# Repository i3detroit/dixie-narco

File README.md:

# dixie-narco
Replacement controller for a Dixie-Narco drink vending machine

Initial reverse-engineering and machine details located in the history of the [equipment page](https://www.i3detroit.org/wiki/Dixie_Narco_Soda_Machine), which will be a living document for the current status of the machine.

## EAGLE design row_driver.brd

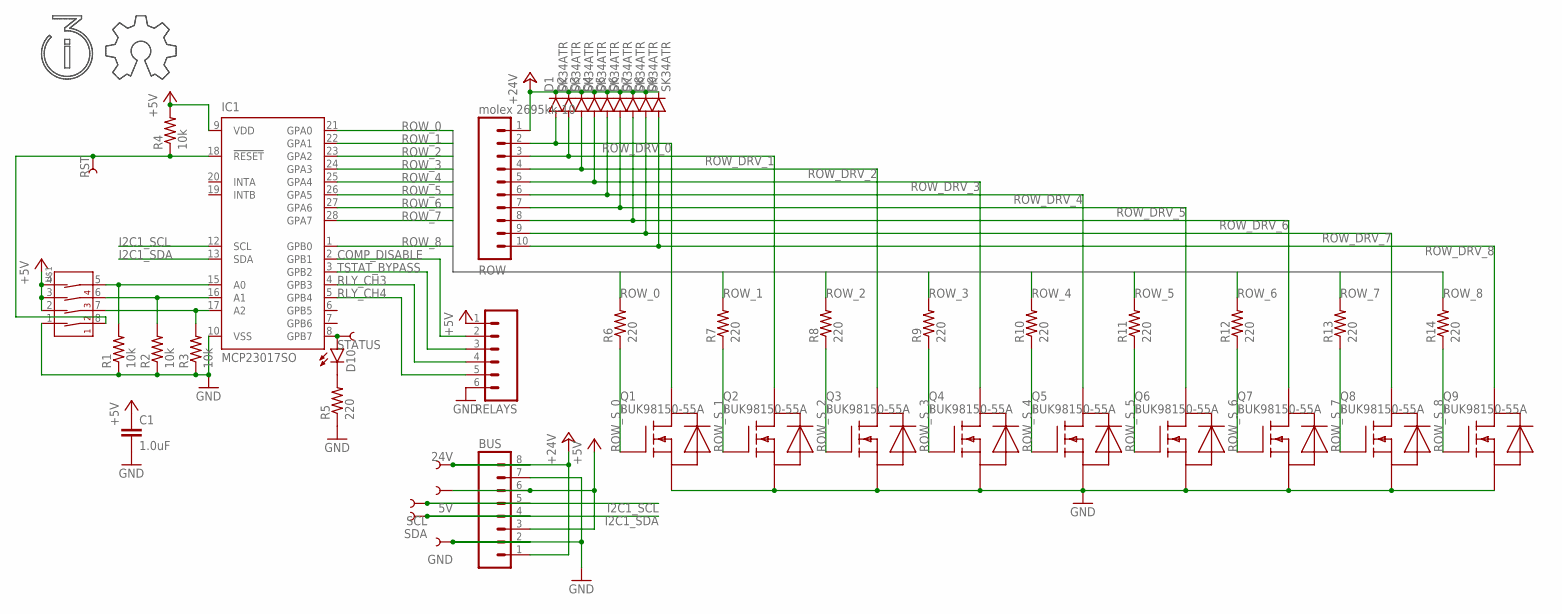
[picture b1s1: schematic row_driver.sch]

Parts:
5V, 24V: TEST-POINTTP_15TH_THRU; TP_15TH
BUS: M08FEMALE_LOCK; 1X08_FEMALE_LOCK
C1: 1.0uF; 0603-CAP
D1, D2, D3, D4, D5, D6, D7, D8, D9: SK34ATR; SMA-DIODE
D10: LED1206; LED-1206
GND: TEST-POINTTP_15TH_THRU; TP_15TH
IC1: MCP23017SO; SO28W
Q1, Q2, Q3, Q4, Q5, Q6, Q7, Q8, Q9: BUK98150-55A; SOT223
R1, R2, R3, R4: 10k; 0805
R5, R6, R7, R8, R9, R10, R11, R12, R13, R14: 220; 0805
RELAYS: M06LOCK; 1X06_LOCK
ROW: molex 2695kk-10; 1X10_LOCK
RST: TEST-POINTTP_15TH_THRU; TP_15TH
SCL: TEST-POINTTP_15TH_THRU; TP_15TH
SDA: TEST-POINTTP_15TH_THRU; TP_15TH
STATUS: TEST-POINTTP_15TH_THRU; TP_15TH
U$1: 4-POS-DIP; 4-POS-DIP-SMD
U$2: I3LOGO
U$4: OSHWLOGO

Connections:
+5V: 5V.P$1, BUS.3, BUS.6, C1.1, IC1.9 (VDD), R4.2, RELAYS.1, U$1.2 (2A), U$1.3 (3A), U$1.4 (4A)
+24V: 24V.P$1, BUS.1, BUS.8, D1.C, D2.C, D3.C, D4.C, D5.C, D6.C, D7.C, D8.C, D9.C, ROW.1
A0: IC1.15 (A0), R1.2, U$1.5 (4B)
A1: IC1.16 (A1), R2.2, U$1.6 (3B)
A2: IC1.17 (A2), R3.2, U$1.7 (2B)
COMP_DISABLE: IC1.2 (GPB1), RELAYS.2
GND: BUS.2, BUS.7, C1.2, GND.P$1, IC1.10 (VSS), Q1.3 (S), Q2.3 (S), Q3.3 (S), Q4.3 (S), Q5.3 (S), Q6.3 (S), Q7.3 (S), Q8.3 (S), Q9.3 (S), R1.1, R2.1, R3.1, R5.1, RELAYS.6, U$1.1 (1A)
I2C1_SCL: BUS.5, IC1.12 (SCL), SCL.P$1
I2C1_SDA: BUS.4, IC1.13 (SDA), SDA.P$1
unnamed: D10.C, R5.2
RLY_CH3: IC1.4 (GPB3), RELAYS.4
RLY_CH4: IC1.5 (GPB4), RELAYS.5
ROW_0: IC1.21 (GPA0), R6.2
ROW_1: IC1.22 (GPA1), R7.2
ROW_2: IC1.23 (GPA2), R8.2
ROW_3: IC1.24 (GPA3), R9.2
ROW_4: IC1.25 (GPA4), R10.2
ROW_5: IC1.26 (GPA5), R11.2
ROW_6: IC1.27 (GPA6), R12.2
ROW_7: IC1.28 (GPA7), R13.2
ROW_8: IC1.1 (GPB0), R14.2
ROW_DRV_0: D1.A, Q1.2 (D), Q1.4 (D), ROW.2
ROW_DRV_1: D2.A, Q2.2 (D), Q2.4 (D), ROW.3
ROW_DRV_2: D3.A, Q3.2 (D), Q3.4 (D), ROW.4
ROW_DRV_3: D4.A, Q4.2 (D), Q4.4 (D), ROW.5
ROW_DRV_4: D5.A, Q5.2 (D), Q5.4 (D), ROW.6
ROW_DRV_5: D6.A, Q6.2 (D), Q6.4 (D), ROW.7
ROW_DRV_6: D7.A, Q7.2 (D), Q7.4 (D), ROW.8
ROW_DRV_7: D8.A, Q8.2 (D), Q8.4 (D), ROW.9
ROW_DRV_8: D9.A, Q9.2 (D), Q9.4 (D), ROW.10
ROW_S_0: Q1.1 (G), R6.1
ROW_S_1: Q2.1 (G), R7.1
ROW_S_2: Q3.1 (G), R8.1
ROW_S_3: Q4.1 (G), R9.1
ROW_S_4: Q5.1 (G), R10.1
ROW_S_5: Q6.1 (G), R11.1
ROW_S_6: Q7.1 (G), R12.1
ROW_S_7: Q8.1 (G), R13.1
ROW_S_8: Q9.1 (G), R14.1
RST: IC1.18 (!RESET), R4.1, RST.P$1, U$1.8 (1B)
STATUS: D10.A, IC1.8 (GPB7), STATUS.P$1
TSTAT_BYPASS: IC1.3 (GPB2), RELAYS.3

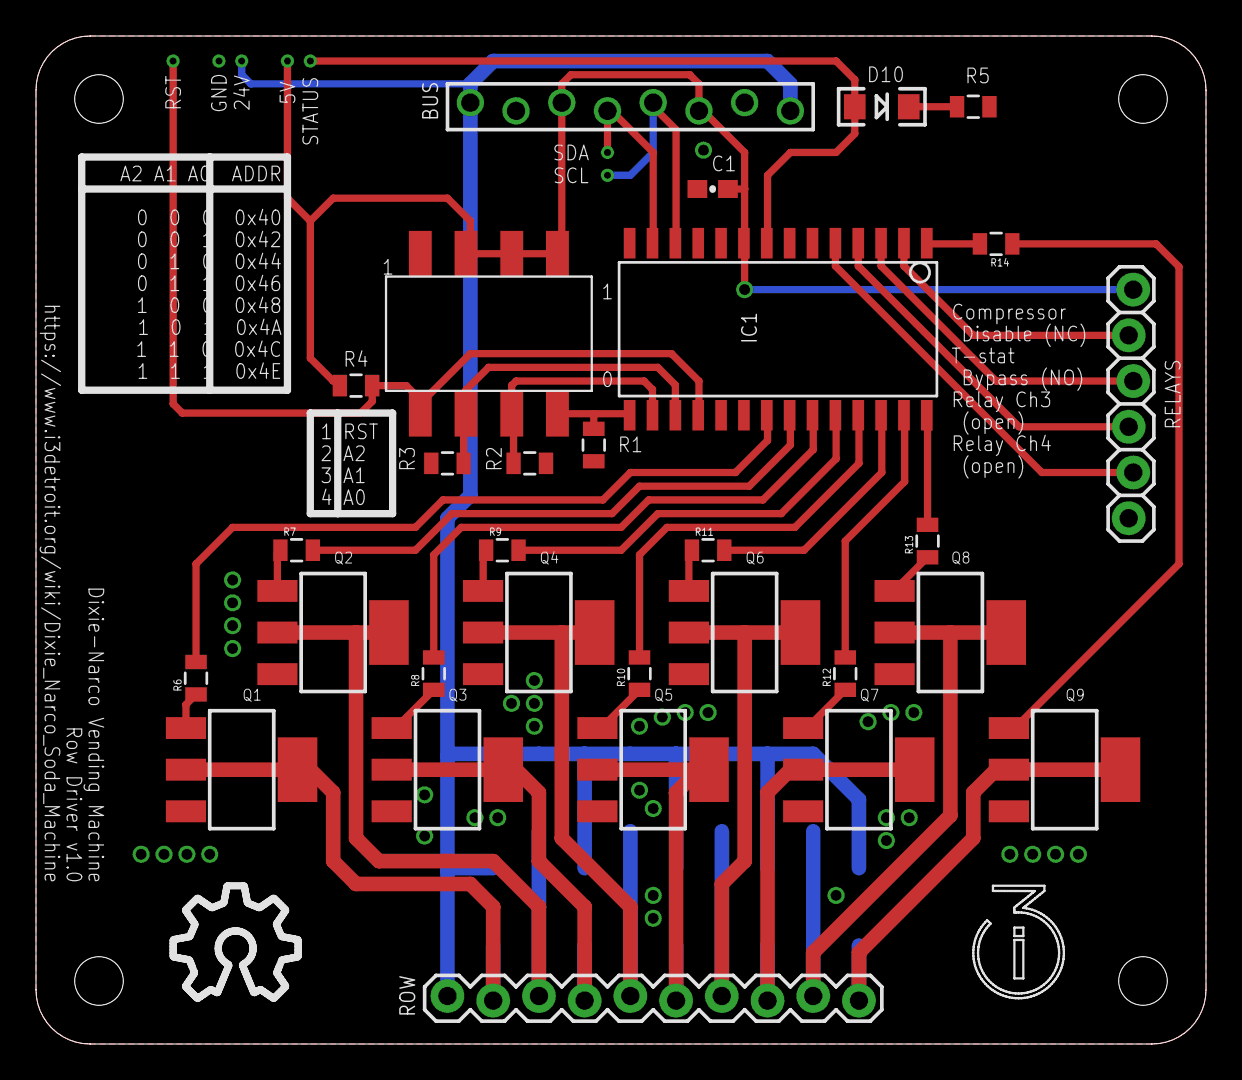
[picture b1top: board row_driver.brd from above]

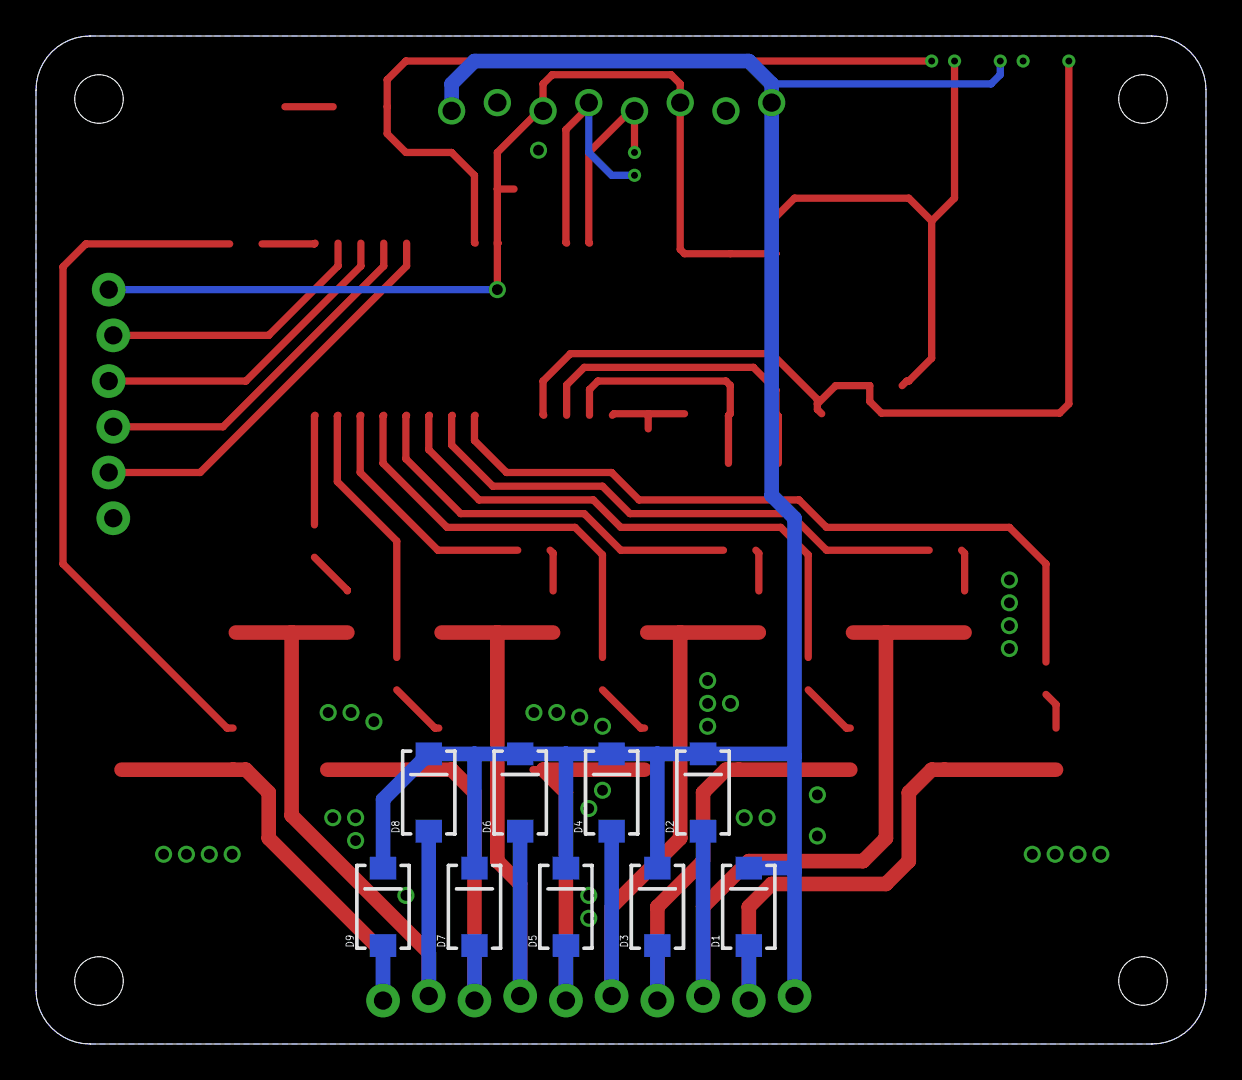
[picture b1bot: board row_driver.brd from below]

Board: 2 copper layers, 65.0 x 56.0 mm, 48 parts (9 on the bottom side), 42 nets.

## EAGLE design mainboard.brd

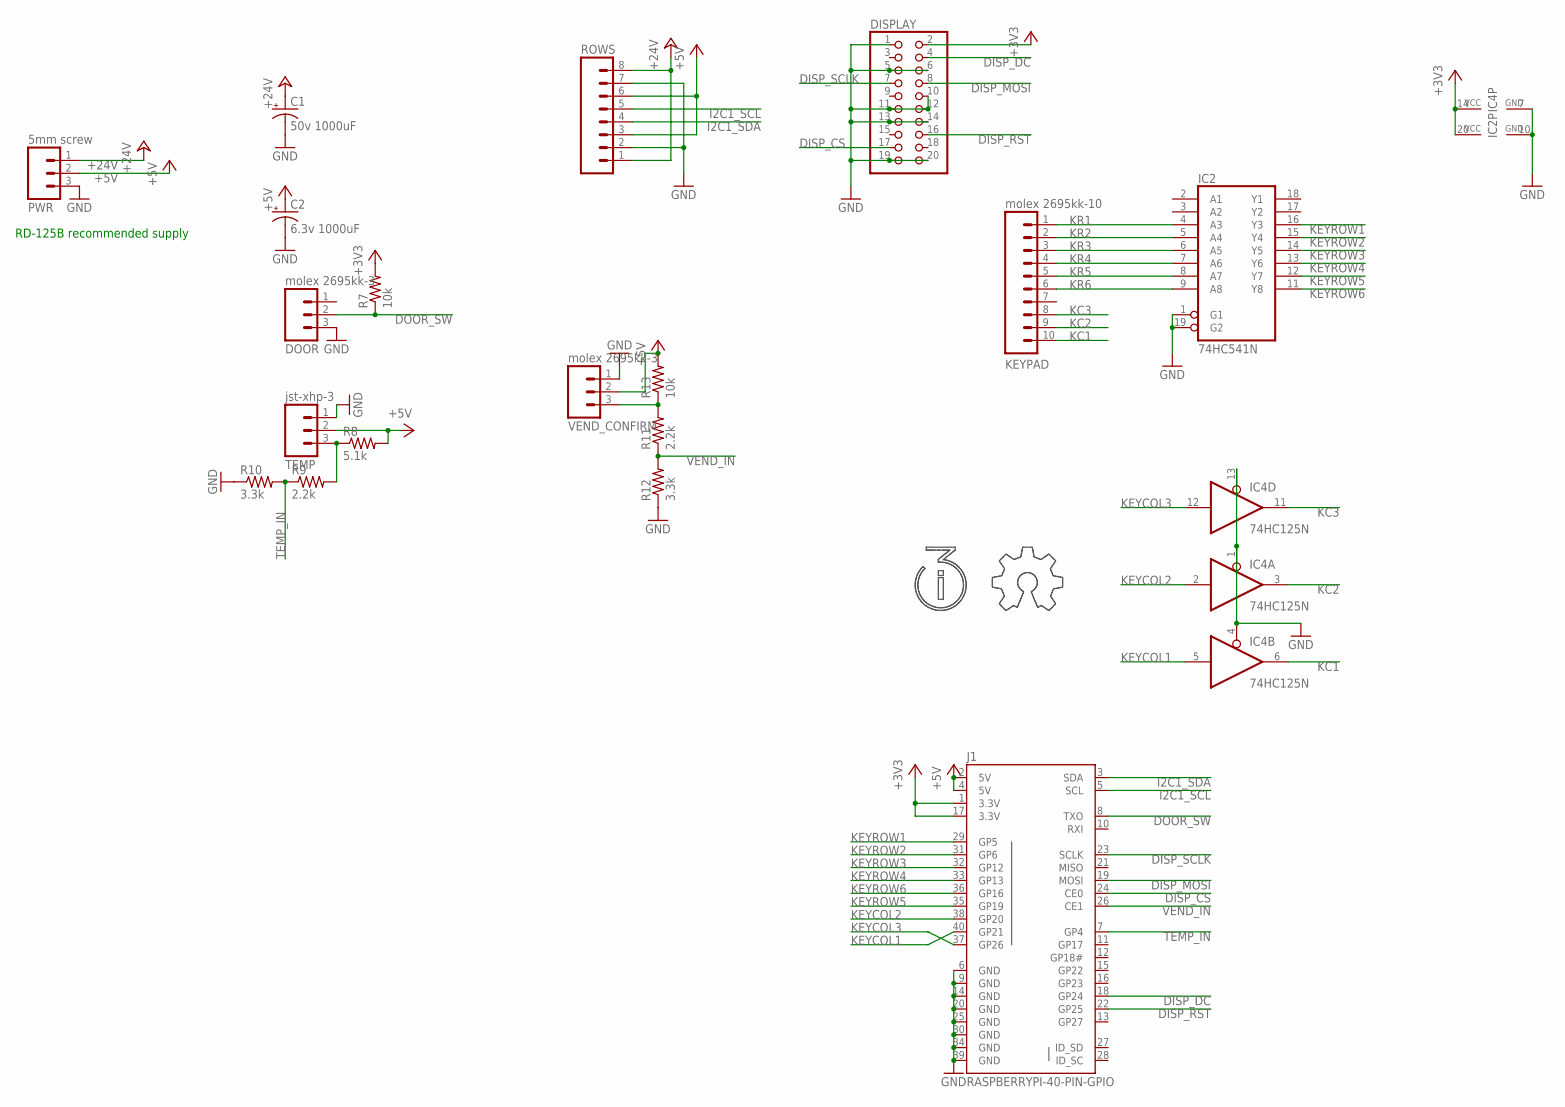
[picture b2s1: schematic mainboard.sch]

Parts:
C1: 50v 1000uF; CPOL-RADIAL-1000UF-25V
C2: 6.3v 1000uF; CPOL-RADIAL-1000UF-25V
DISPLAY: PINHD-2X10; 2X10
DOOR: molex 2695kk-3; MOLEX-1X3
IC2: 74HC541N; DIL20
IC4: 74HC125N; DIL14
J1: RASPBERRYPI-40-PIN-GPIO; 2X20-SHROUDED
KEYPAD: molex 2695kk-10; 1X10_LOCK
PWR: 5mm screw; SCREWTERMINAL-5MM-3
R7, R13: 10k; 1206
R8: 5.1k; 1206
R9, R11: 2.2k; 1206
R10, R12: 3.3k; 1206
ROWS: M08FEMALE_LOCK; 1X08_FEMALE_LOCK
TEMP: jst-xhp-3; 1X03
U$1: I3LOGO
U$2: OSHWLOGO
VEND_CONFIRM: molex 2695kk-3; MOLEX-1X3

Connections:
+3V3: DISPLAY.2, IC2.20 (VCC), IC4.14 (VCC), J1.1 (3.3V), J1.17 (3.3V), R7.2
+5V: C2.+, J1.2 (5V), J1.4 (5V), PWR.2, R8.2, R13.2, ROWS.3, ROWS.6, TEMP.2, VEND_CONFIRM.2
+24V: C1.+, PWR.1, ROWS.1, ROWS.8
DISP_CS: DISPLAY.17, J1.24 (CE0)
DISP_DC: DISPLAY.4, J1.18 (GP24)
DISP_MOSI: DISPLAY.8, J1.19 (MOSI)
DISP_RST: DISPLAY.16, J1.22 (GP25)
DISP_SCLK: DISPLAY.7, J1.23 (SCLK)
DOOR_SW: DOOR.2, J1.8 (TXO), R7.1
GND: C1.-, C2.-, DISPLAY.1, DISPLAY.5, DISPLAY.6, DISPLAY.10, DISPLAY.11, DISPLAY.12, DISPLAY.13, DISPLAY.14, DISPLAY.19, DISPLAY.20, DOOR.3, IC2.1 (G1), IC2.10 (GND), IC2.19 (G2), IC4.1 (OE), IC4.4 (OE), IC4.7 (GND), IC4.13 (OE), J1.6 (GND), J1.9 (GND), J1.14 (GND), J1.20 (GND), J1.25 (GND), J1.30 (GND), J1.34 (GND), J1.39 (GND), PWR.3, R10.1, R12.1, ROWS.2, ROWS.7, TEMP.1, VEND_CONFIRM.1
I2C1_SCL: J1.5 (SCL), ROWS.5
I2C1_SDA: J1.3 (SDA), ROWS.4
KC1: IC4.6 (O), KEYPAD.10
KC2: IC4.3 (O), KEYPAD.9
KC3: IC4.11 (O), KEYPAD.8
KEYCOL1: IC4.5 (I), J1.40 (GP21)
KEYCOL2: IC4.2 (I), J1.38 (GP20)
KEYCOL3: IC4.12 (I), J1.37 (GP26)
KEYROW1: IC2.16 (Y3), J1.29 (GP5)
KEYROW2: IC2.15 (Y4), J1.31 (GP6)
KEYROW3: IC2.14 (Y5), J1.32 (GP12)
KEYROW4: IC2.13 (Y6), J1.33 (GP13)
KEYROW5: IC2.12 (Y7), J1.35 (GP19)
KEYROW6: IC2.11 (Y8), J1.36 (GP16)
KR1: IC2.4 (A3), KEYPAD.1
KR2: IC2.5 (A4), KEYPAD.2
KR3: IC2.6 (A5), KEYPAD.3
KR4: IC2.7 (A6), KEYPAD.4
KR5: IC2.8 (A7), KEYPAD.5
KR6: IC2.9 (A8), KEYPAD.6
unnamed: R8.1, R9.2, TEMP.3
unnamed: R11.2, R13.1, VEND_CONFIRM.3
TEMP_IN: J1.7 (GP4), R9.1, R10.2
VEND_IN: J1.26 (CE1), R11.1, R12.2

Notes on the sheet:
RD-125B recommended supply

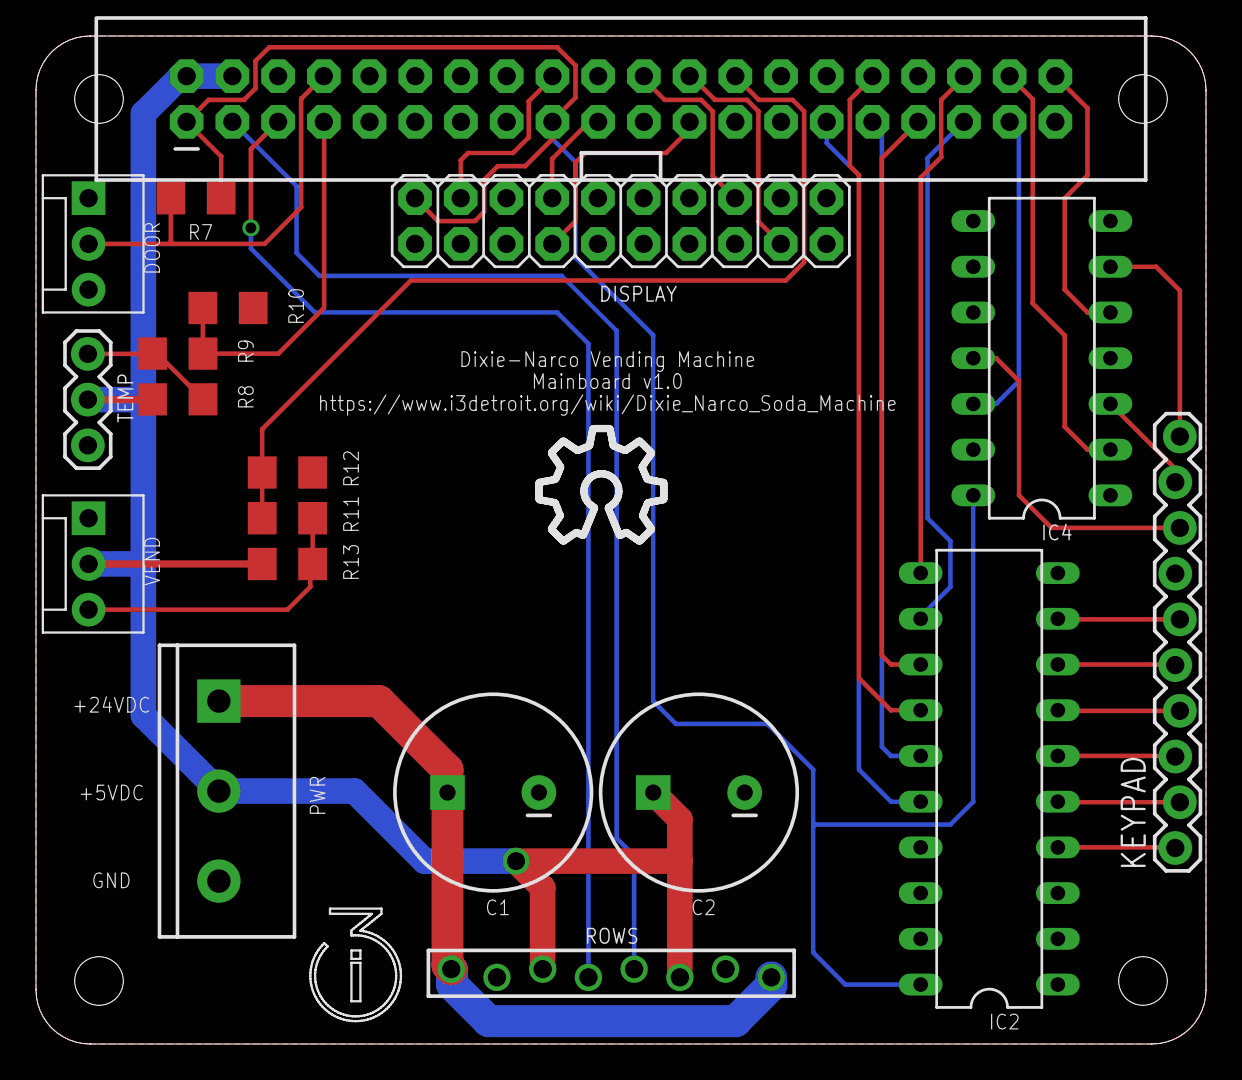
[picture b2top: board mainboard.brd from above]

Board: 2 copper layers, 65.0 x 56.0 mm, 21 parts (0 on the bottom side), 34 nets.

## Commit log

2018-12-31 Row driver schematic and board complete, ready for testing.
2019-01-05 Initial draft of mainboard.
2019-01-05 Added relay header for the ubiquitous 4-channel relay boards. Two are immediately assigned: one acts in NC in series with the compressor (so the controller can interrupt compressor power on demand, b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
2019-02-09 Completed mainboard design edits; buffers for keypad, reworked 5V feed.
2019-02-09 Added GND vias on row_driver.
2019-02-09 No the one-wire sensor does not need a $0.252 resistor as a pull-up the $0.0254 ones are fine kthxbai.
2019-03-16 Organizantional cleanup
2019-03-16 Row driver test helper script
2019-03-23 Added adapter plate for OLED screen to machine service door posts.
2019-03-27 Added pin mapping file maybe this is even readable by machine.
2019-04-20 Added SDK to ignore
2019-04-20 Remapped slot labels
2019-04-21 Base keypad scan code
2019-04-21 Pulldowns are useful
2019-04-21 ignore eagle lockfiles
2019-04-21 corrected keypad pins
2019-04-21 add mode bit for executable
2019-04-21 All debounce and polarity confirmed to work
2019-04-21 rename row driver
2019-04-21 modularized row driver
2019-04-21 fixing mode bits
2019-04-21 so syntax is important
2019-04-21 as is using the right attributes...
2019-04-21 moar syntax
2019-04-21 modularized keypad reader
2019-04-21 Very stubby vending code
2019-04-21 mode bit
2019-04-21 None is bad for comparison
2019-04-21 Working changes
2019-04-21 intial display helper
2019-04-21 FIxed font
2019-04-21 tweaks to fix default display
2019-04-21 shortened debounce period for cleaner presses
2019-04-21 base MVP minus pay
2019-04-21 Timer for screen blanking to save OLED

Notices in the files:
parts and their libraries:
SparkFun-Capacitors: Licensing: Creative Commons ShareAlike 4.0 International - https://creativecommons.org/licenses/by-sa/4.0
